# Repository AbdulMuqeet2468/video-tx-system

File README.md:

# video-tx-system

Under progress...

## Trail 1
Planned to use TPS54560BQDDARQ1 IC from Texas Instruments; 50V input and 5V 6A output. 
- Footprint was too big
- Inductor (15uH 11A) had bigger footprint and not available

## Trail 2
Using LM76003RNPR with lesser eficiency and better footprint. 
- Completed simulation
- Created symbols and footprints for missing components
- completed schematic

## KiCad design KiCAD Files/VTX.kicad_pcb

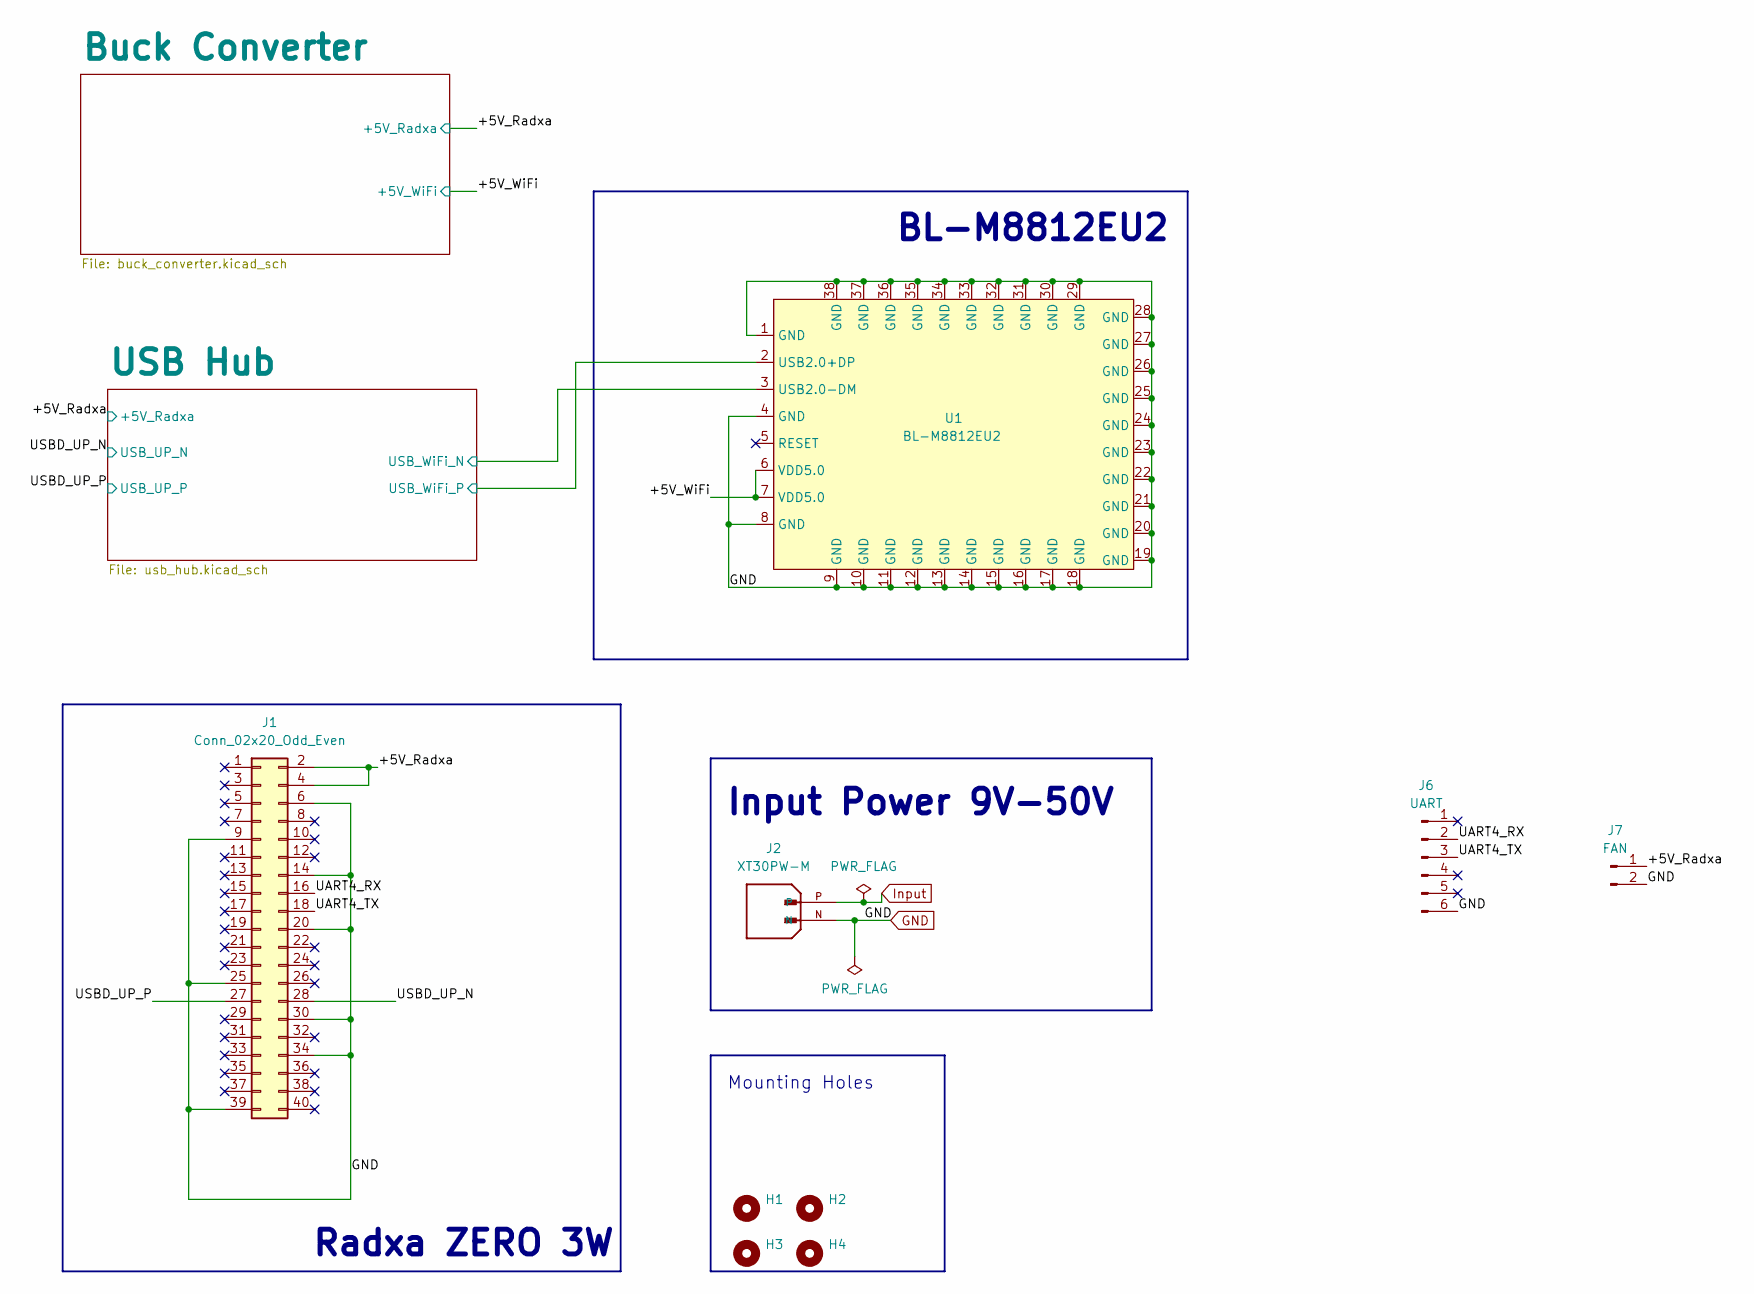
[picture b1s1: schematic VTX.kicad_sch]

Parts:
H1, H2, H3, H4: MountingHole; MountingHole_3mm
J1: Conn_02x20_Odd_Even; PinHeader_2x20_P2.54mm_Vertical
J2: XT30PW-M; AMASS_XT30PW-M; PARTREV 1.2
J6: UART; JST_GH_SM06B-GHS-TB_1x06-1MP_P1.25mm_Horizontal
J7: FAN; JST_GH_SM02B-GHS-TB_1x02-1MP_P1.25mm_Horizontal
U1: BL-M8812EU2

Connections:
+5V_Radxa: J1.2, J1.4, J7.1; also elsewhere on the board
+5V_WiFi: U1.6 (VDD5.0), U1.7 (VDD5.0); also elsewhere on the board
/UART4_RX: J1.16, J6.2
/UART4_TX: J1.18, J6.3
/USB Hub/USB_WiFi_N: U1.3 (USB2.0-DM); also elsewhere on the board
/USB Hub/USB_WiFi_P: U1.2 (USB2.0+DP); also elsewhere on the board
/USBD_UP_N: J1.28; also elsewhere on the board
/USBD_UP_P: J1.27; also elsewhere on the board
GND: J1.6, J1.9, J1.14, J1.20, J1.25, J1.30, J1.34, J1.39, J2.N, J6.6, J7.2, U1.1 (GND), U1.4 (GND), U1.8 (GND), U1.9 (GND), U1.10 (GND), U1.11 (GND), U1.12 (GND), U1.13 (GND), U1.14 (GND), U1.15 (GND), U1.16 (GND), U1.17 (GND), U1.18 (GND), U1.19 (GND), U1.20 (GND), U1.21 (GND), U1.22 (GND), U1.23 (GND), U1.24 (GND), U1.25 (GND), U1.26 (GND), U1.27 (GND), U1.28 (GND), U1.29 (GND), U1.30 (GND), U1.31 (GND), U1.32 (GND), U1.33 (GND), U1.34 (GND), U1.35 (GND), U1.36 (GND), U1.37 (GND), U1.38 (GND); also elsewhere on the board
Input: J2.P; also elsewhere on the board

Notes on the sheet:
BL-M8812EU2
Mounting Holes
Radxa ZERO 3W
Input Power 9V-50V

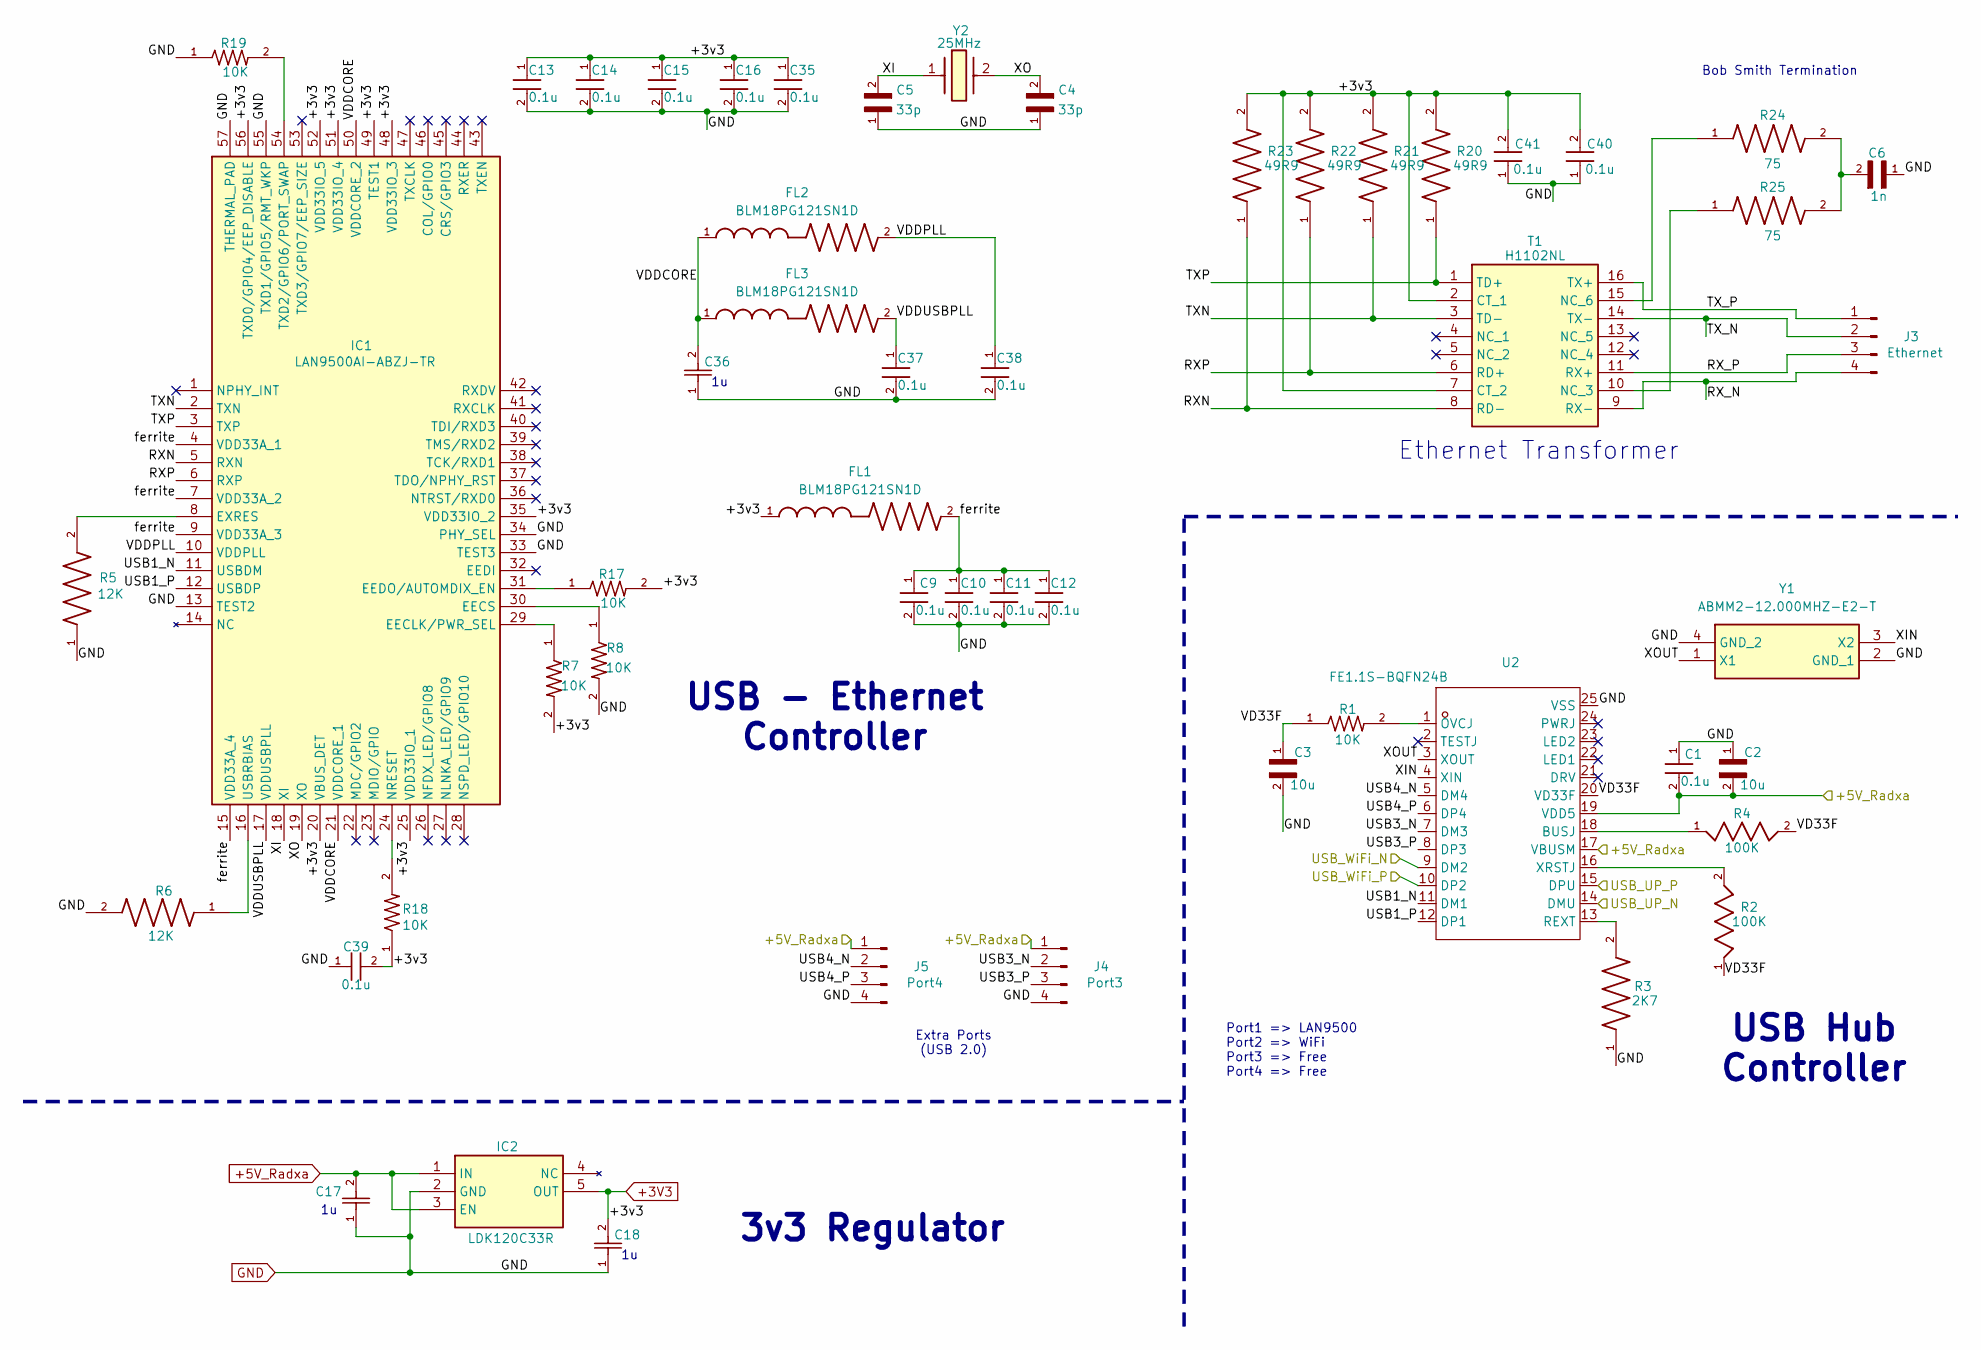
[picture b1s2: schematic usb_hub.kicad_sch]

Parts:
C1, C9, C10, C11, C12, C13, C14, C15, C16, C35, C37, C38, C39, C40, C41: 0.1u; 100nF0603
C2, C3: 10u; CL10A106KQ8NNNC
C4, C5: 33p; TCC0402COG330J500AT; PARTREV 2015-02-10
C6: 1n; C1206C102JGRACTU
C17, C18: 1uF; CC0805KKX7R6BB225; VOLTAGERATING 10V; TOLERANCE ±10%; MPN CC0805KKX7R6BB225
C36: 1uF; C0805X474K101T; VOLTAGERATING 10V; TOLERANCE ±10%; MPN CC0805KKX7R6BB225
FL1, FL2, FL3: BLM18PG121SN1D
IC1: LAN9500AI-ABZJ-TR; Manufacturer_Part_Number LAN9500AI-ABZJ-TR
IC2: LDK120C33R; Manufacturer_Part_Number LDK120C33R
J3: Ethernet; JST_GH_SM04B-GHS-TB_1x04-1MP_P1.25mm_Horizontal
J4: Port3; JST_GH_SM04B-GHS-TB_1x04-1MP_P1.25mm_Horizontal
J5: Port4; JST_GH_SM04B-GHS-TB_1x04-1MP_P1.25mm_Horizontal
R1, R7, R8, R17, R18, R19: 10K; RC0603JR-0710KL; DigiKey_Part_Number 311-10KGRCT-ND
R2, R4: 100K; RC0402FR-07100KL
R3: 2K7; RC0805FR-072K7L
R5, R6: 12K; RC0805FR-0712KL
R20, R21, R22, R23: 49R9; RC0805FR-0749R9L
R24, R25: 75; RC0805FR-0775RL
T1: H1102NL; Manufacturer_Part_Number H1102NL
U2: FE1.1S-BQFN24B; VOLTAGE - SUPPLY 4.5V~5.5V；3V~3.6V; MANUFACTURERPART FE1.1S-BQFN24B; LCSC PART NAME USB 2.0 4-端口集线器控制器
Y1: ABMM2-12.000MHZ-E2-T; ABMM2-12MHz; Manufacturer_Part_Number ABMM2-12.000MHZ-E2-T
Y2: 25MHz; ABM7-25MHz; Manufacturer_Part_Number ABM7-25.000MHZ-D2Y-T

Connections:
+3V3: C13.1, C14.1, C15.1, C16.1, C18.2, C35.1, C39.2, C40.2, C41.2, FL1.1, IC1.20 (VBUS_DET), IC1.25 (VDD33IO_1), IC1.35 (VDD33IO_2), IC1.48 (VDD33IO_3), IC1.49 (TEST1), IC1.51 (VDD33IO_4), IC1.52 (VDD33IO_5), IC1.56 (TXD0/GPIO4/EEP_DISABLE), IC2.5 (OUT), R7.2, R17.2, R18.1, R20.2, R21.2, R22.2, R23.2, T1.2 (CT_1), T1.7 (CT_2)
+5V_Radxa: C1.2, C2.2, C17.2, IC2.1 (IN), IC2.3 (EN), J4.1, J5.1, U2.17 (VBUSM), U2.19 (VDD5); also elsewhere on the board
/USB Hub/RXN: IC1.5 (RXN), R23.1, T1.8 (RD-)
/USB Hub/RXP: IC1.6 (RXP), R22.1, T1.6 (RD+)
/USB Hub/RX_N: J3.4, T1.9 (RX-)
/USB Hub/RX_P: J3.3, T1.11 (RX+)
/USB Hub/TXN: IC1.2 (TXN), R21.1, T1.3 (TD-)
/USB Hub/TXP: IC1.3 (TXP), R20.1, T1.1 (TD+)
/USB Hub/TX_N: J3.2, T1.14 (TX-)
/USB Hub/TX_P: J3.1, T1.16 (TX+)
/USB Hub/USB1_N: IC1.11 (USBDM), U2.11 (DM1)
/USB Hub/USB1_P: IC1.12 (USBDP), U2.12 (DP1)
/USB Hub/USB3_N: J4.2, U2.7 (DM3)
/USB Hub/USB3_P: J4.3, U2.8 (DP3)
/USB Hub/USB4_N: J5.2, U2.5 (DM4)
/USB Hub/USB4_P: J5.3, U2.6 (DP4)
/USB Hub/USB_WiFi_N: U2.9 (DM2); also elsewhere on the board
/USB Hub/USB_WiFi_P: U2.10 (DP2); also elsewhere on the board
/USB Hub/VD33F: C3.1, R1.1, R2.1, R4.2, U2.20 (VD33F)
/USB Hub/VDDCORE: C36.2, FL2.1, FL3.1, IC1.21 (VDDCORE_1), IC1.50 (VDDCORE_2)
/USB Hub/VDDPLL: C38.1, FL2.2, IC1.10 (VDDPLL)
/USB Hub/VDDUSBPLL: C37.1, FL3.2, IC1.17 (VDDUSBPLL)
/USB Hub/XI: C5.2, IC1.18 (XI), Y2.1
/USB Hub/XIN: U2.4 (XIN), Y1.3 (X2)
/USB Hub/XO: C4.2, IC1.19 (XO), Y2.2
/USB Hub/XOUT: U2.3 (XOUT), Y1.1 (X1)
/USB Hub/ferrite: C9.1, C10.1, C11.1, C12.1, FL1.2, IC1.4 (VDD33A_1), IC1.7 (VDD33A_2), IC1.9 (VDD33A_3), IC1.15 (VDD33A_4)
/USBD_UP_N: U2.14 (DMU); also elsewhere on the board
/USBD_UP_P: U2.15 (DPU); also elsewhere on the board
GND: C1.1, C2.1, C3.2, C4.1, C5.1, C6.1, C9.2, C10.2, C11.2, C12.2, C13.2, C14.2, C15.2, C16.2, C17.1, C18.1, C35.2, C36.1, C37.2, C38.2, C39.1, C40.1, C41.1, IC1.13 (TEST2), IC1.33 (TEST3), IC1.34 (PHY_SEL), IC1.55 (TXD1/GPIO5/RMT_WKP), IC1.57 (THERMAL_PAD), IC2.2 (GND), J4.4, J5.4, R3.1, R5.1, R6.2, R8.2, R19.1, U2.25 (VSS), Y1.2 (GND_1), Y1.4 (GND_2); also elsewhere on the board
unnamed: C6.2, R24.2, R25.2
unnamed: IC1.29 (EECLK/PWR_SEL), R7.1
unnamed: IC1.30 (EECS), R8.1
unnamed: IC1.31 (EEDO/AUTOMDIX_EN), R17.1
unnamed: IC1.8 (EXRES), R5.2
unnamed: IC1.24 (NRESET), R18.2
unnamed: IC1.54 (TXD2/GPIO6/PORT_SWAP), R19.2
unnamed: IC1.16 (USBRBIAS), R6.1
unnamed: R25.1, T1.10 (NC_3)
unnamed: R24.1, T1.15 (NC_6)
unnamed: R4.1, U2.18 (BUSJ)
unnamed: R1.2, U2.1 (OVCJ)
unnamed: R3.2, U2.13 (REXT)
unnamed: R2.2, U2.16 (XRSTJ)

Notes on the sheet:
Extra Ports (USB 2.0)
Ethernet Transformer
Bob Smith Termination
Port1 => LAN9500 Port2 => WiFi Port3 => Free Port4 => Free
3v3 Regulator
USB Hub Controller
USB - Ethernet Controller

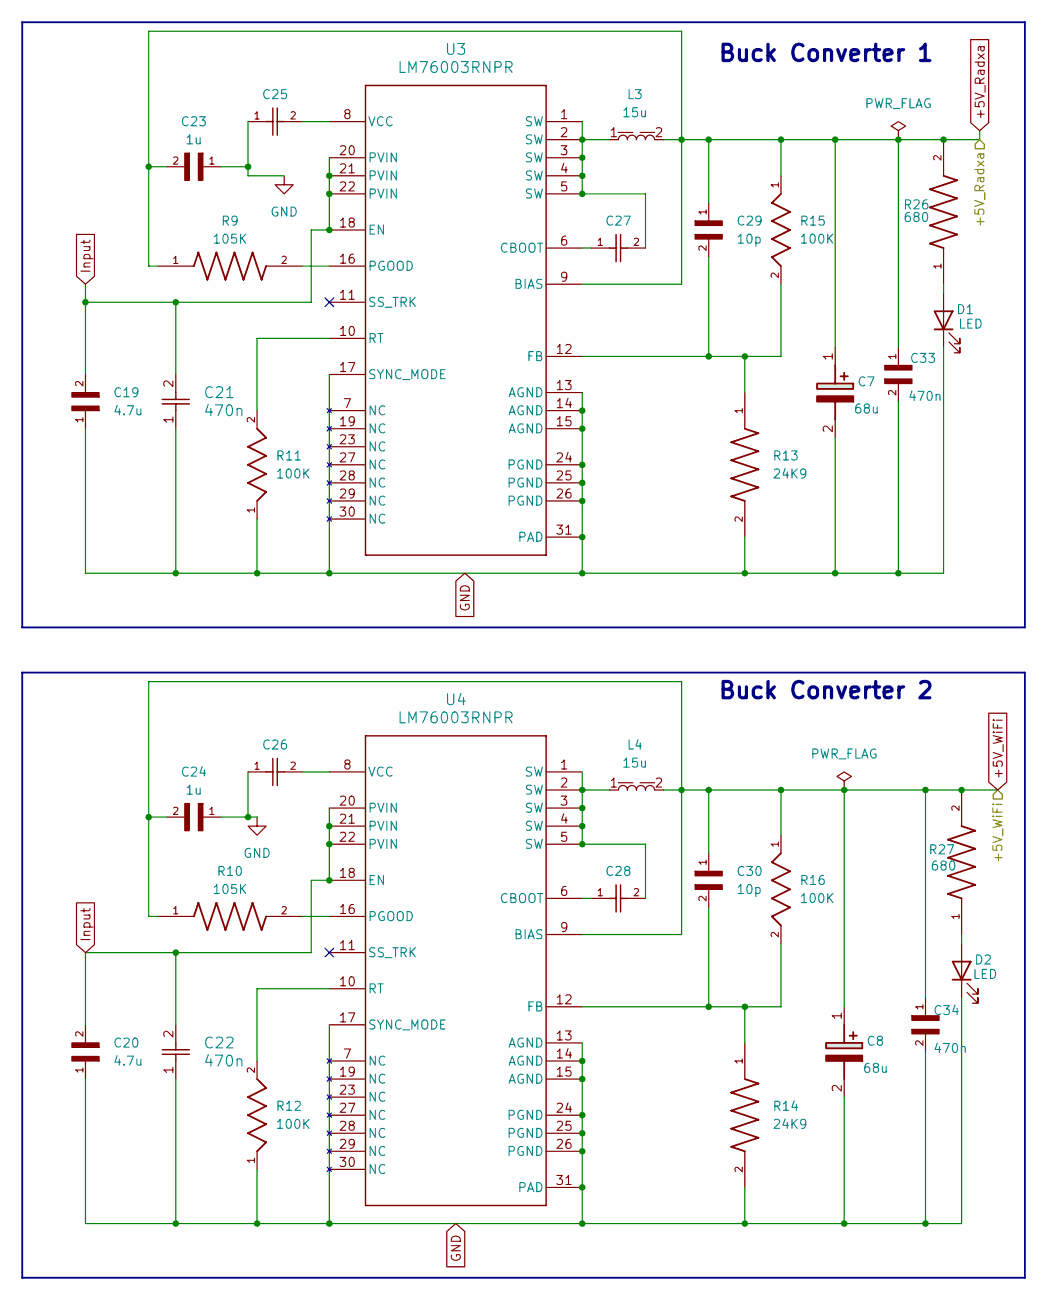
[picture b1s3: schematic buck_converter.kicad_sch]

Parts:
C7, C8: 68u; 10SVPC68MV; Manufacturer_Part_Number 10SVPC68MV
C19, C20: 4.7u; CS3225X7R475K101NRK
C21, C22: 470n; C0805X474K101T
C23, C24: 1u; CC0603KRX5R6BB105
C25, C26: 2.2uF; CC0805KKX7R6BB225; VOLTAGERATING 10V; TOLERANCE ±10%; MPN CC0805KKX7R6BB225
C27, C28: 2.2uF; CS1005X7R474K6R3NR; VOLTAGERATING 10V; TOLERANCE ±10%; MPN CC0805KKX7R6BB225
C29, C30: 10p; 10pF16V
C33, C34: 470n; CL10A474KB8NNNC
D1, D2: LED; RC0805FR-07680RL
L3, L4: 6060_78439346150; L78439346150; Part Number 78439346150
R9, R10: 105K; RC1206FR-07105KL
R11, R12, R15, R16: 100K; RC0402FR-07100KL
R13, R14: 24K9; AC0402FR-0724K9L
R26, R27: 680; RC0805FR-07680RL
U3, U4: LM76003RNPR

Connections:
+5V_Radxa: C7.1 (+), C23.2, C29.1, C33.1, L3.2, R9.1, R15.1, R26.2, U3.9 (BIAS); also elsewhere on the board
+5V_WiFi: C8.1 (+), C24.2, C30.1, C34.1, L4.2, R10.1, R16.1, R27.2, U4.9 (BIAS); also elsewhere on the board
GND: C7.2 (-), C8.2 (-), C19.1, C20.1, C21.1, C22.1, C23.1, C24.1, C25.1, C26.1, C33.2, C34.2, D1.1 (K), D2.1 (K), R11.1, R12.1, R13.2, R14.2, U3.13 (AGND), U3.14 (AGND), U3.15 (AGND), U3.17 (SYNC_MODE), U3.24 (PGND), U3.25 (PGND), U3.26 (PGND), U3.31 (PAD), U4.13 (AGND), U4.14 (AGND), U4.15 (AGND), U4.17 (SYNC_MODE), U4.24 (PGND), U4.25 (PGND), U4.26 (PGND), U4.31 (PAD); also elsewhere on the board
Input: C19.2, C20.2, C21.2, C22.2, U3.18 (EN), U3.20 (PVIN), U3.21 (PVIN), U3.22 (PVIN), U4.18 (EN), U4.20 (PVIN), U4.21 (PVIN), U4.22 (PVIN); also elsewhere on the board
unnamed: C27.2, L3.1, U3.1 (SW), U3.2 (SW), U3.3 (SW), U3.4 (SW), U3.5 (SW)
unnamed: C28.2, L4.1, U4.1 (SW), U4.2 (SW), U4.3 (SW), U4.4 (SW), U4.5 (SW)
unnamed: D1.2 (A), R26.1
unnamed: D2.2 (A), R27.1
unnamed: C27.1, U3.6 (CBOOT)
unnamed: C29.2, R13.1, R15.2, U3.12 (FB)
unnamed: R9.2, U3.16 (PGOOD)
unnamed: R11.2, U3.10 (RT)
unnamed: C25.2, U3.8 (VCC)
unnamed: C28.1, U4.6 (CBOOT)
unnamed: C30.2, R14.1, R16.2, U4.12 (FB)
unnamed: R10.2, U4.16 (PGOOD)
unnamed: R12.2, U4.10 (RT)
unnamed: C26.2, U4.8 (VCC)

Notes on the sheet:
Buck Converter 1
Buck Converter 2

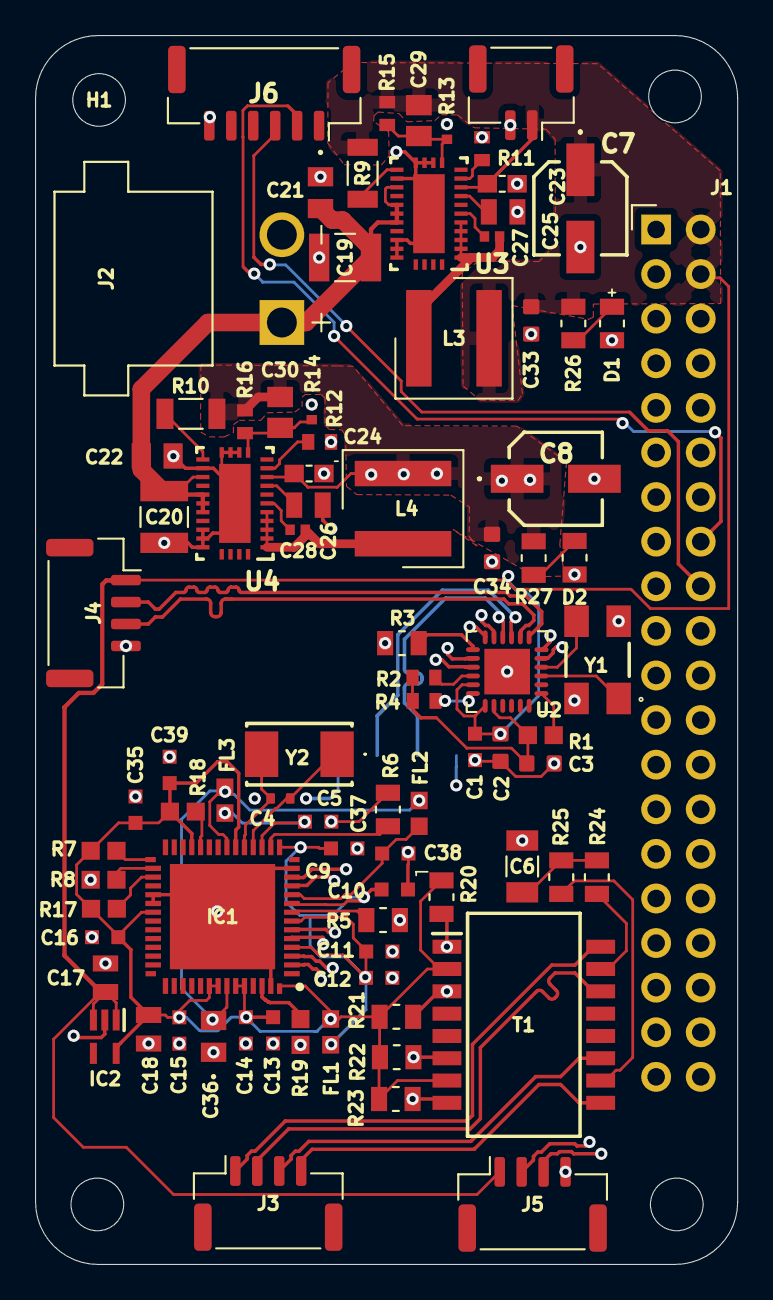
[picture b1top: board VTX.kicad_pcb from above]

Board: 4 copper layers, 40.0 x 70.0 mm, 91 parts (0 on the bottom side), 62 nets.
